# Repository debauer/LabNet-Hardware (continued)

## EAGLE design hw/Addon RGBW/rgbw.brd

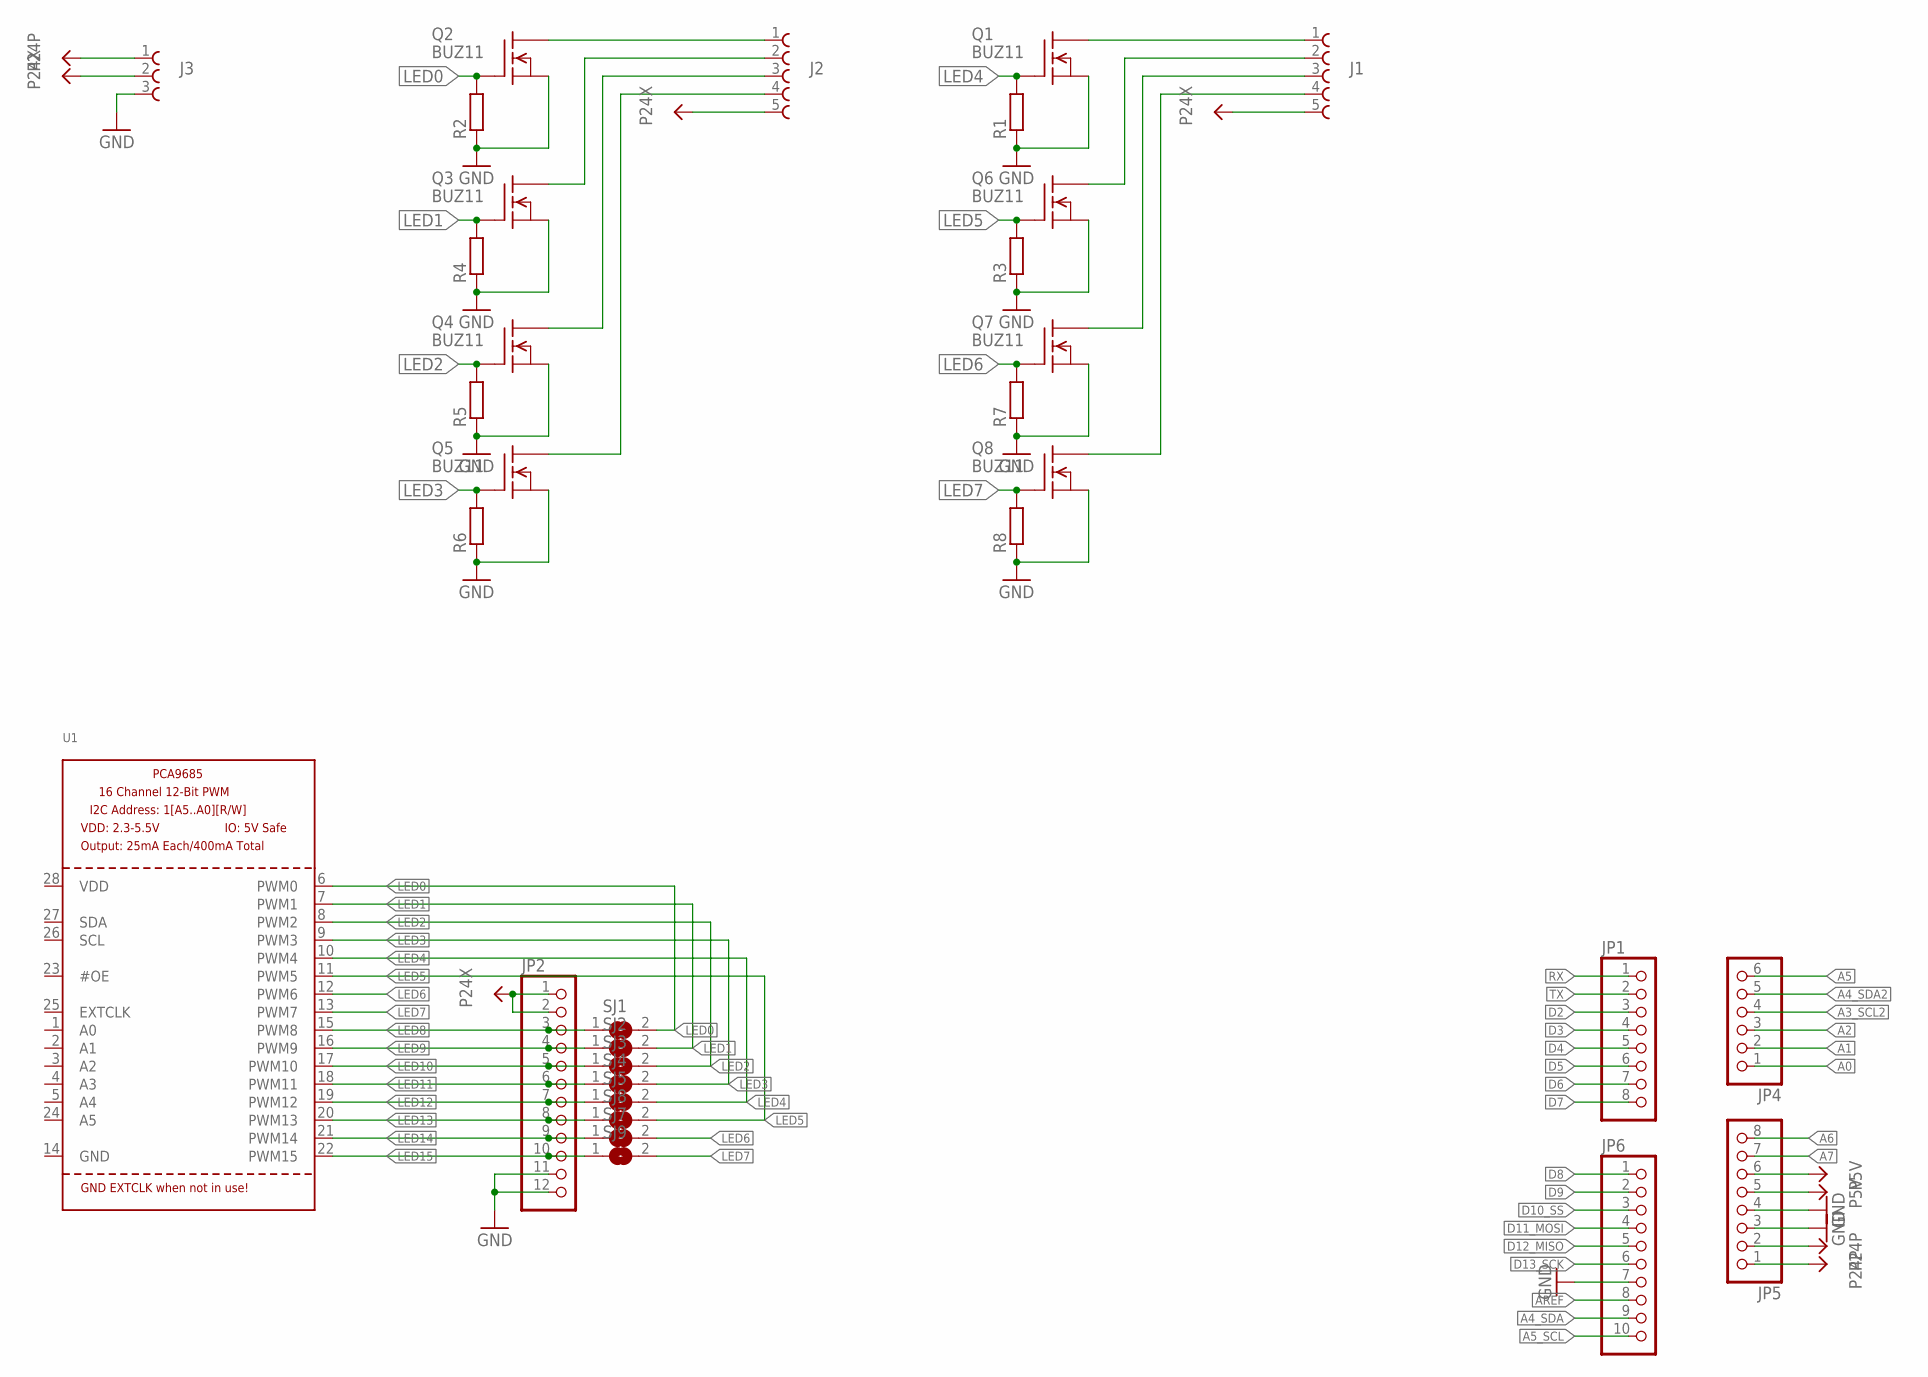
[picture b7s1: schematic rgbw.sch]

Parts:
J1, J2: 691322310005
J3: 691313510003
JP1, JP5: PINHD-1X8; 1X08
JP2: PINHD-1X12; 1X12
JP4: PINHD-1X6; 1X06
JP6: PINHD-1X10; 1X10
Q1, Q2, Q3, Q4, Q5, Q6, Q7, Q8: BUZ11; TO220V
R1, R2, R3, R4, R5, R6, R7, R8: R-EU_R0805; R0805
SJ1, SJ2, SJ3, SJ4, SJ5, SJ7, SJ8, SJ9: SJ
U1: PCA9685; TSSOP28

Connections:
A0: JP4.1
A1: JP4.2
A2: JP4.3
A3_SCL2: JP4.4
A4_SDA: JP6.9
A4_SDA2: JP4.5
A5: JP4.6
A5_SCL: JP6.10
A6: JP5.8
A7: JP5.7
AREF: JP6.8
D2: JP1.3
D3: JP1.4
D4: JP1.5
D5: JP1.6
D6: JP1.7
D7: JP1.8
D8: JP6.1
D9: JP6.2
D10_SS: JP6.3
D11_MOSI: JP6.4
D12_MISO: JP6.5
D13_SCK: JP6.6
GND: J3.3, JP2.11, JP2.12, JP5.3, JP5.4, JP6.7, Q1.3 (S), Q2.3 (S), Q3.3 (S), Q4.3 (S), Q5.3 (S), Q6.3 (S), Q7.3 (S), Q8.3 (S), R1.1, R2.1, R3.1, R4.1, R5.1, R6.1, R7.1, R8.1, U1.14 (GND)
LED0: Q2.1 (G), R2.2, SJ1.2, U1.6 (PWM0)
LED1: Q3.1 (G), R4.2, SJ2.2, U1.7 (PWM1)
LED2: Q4.1 (G), R5.2, SJ3.2, U1.8 (PWM2)
LED3: Q5.1 (G), R6.2, SJ4.2, U1.9 (PWM3)
LED4: Q1.1 (G), R1.2, SJ5.2, U1.10 (PWM4)
LED5: Q6.1 (G), R3.2, SJ8.2, U1.11 (PWM5)
LED6: Q7.1 (G), R7.2, SJ7.2, U1.12 (PWM6)
LED7: Q8.1 (G), R8.2, SJ9.2, U1.13 (PWM7)
LED8: JP2.3, SJ1.1, U1.15 (PWM8)
LED9: JP2.4, SJ2.1, U1.16 (PWM9)
LED10: JP2.5, SJ3.1, U1.17 (PWM10)
LED11: JP2.6, SJ4.1, U1.18 (PWM11)
LED12: JP2.7, SJ5.1, U1.19 (PWM12)
LED13: JP2.8, SJ8.1, U1.20 (PWM13)
LED14: JP2.9, SJ7.1, U1.21 (PWM14)
LED15: JP2.10, SJ9.1, U1.22 (PWM15)
unnamed: J2.1, Q2.2 (D)
unnamed: J2.2, Q3.2 (D)
unnamed: J1.3, Q7.2 (D)
unnamed: J2.3, Q4.2 (D)
unnamed: J2.4, Q5.2 (D)
unnamed: J1.4, Q8.2 (D)
unnamed: J1.1, Q1.2 (D)
unnamed: J1.2, Q6.2 (D)
P5V: JP5.5, JP5.6
P24P: J3.1, JP5.1, JP5.2
P24X: J1.5, J2.5, J3.2, JP2.1, JP2.2
RX: JP1.1
TX: JP1.2
VDD: U1.28 (VDD)

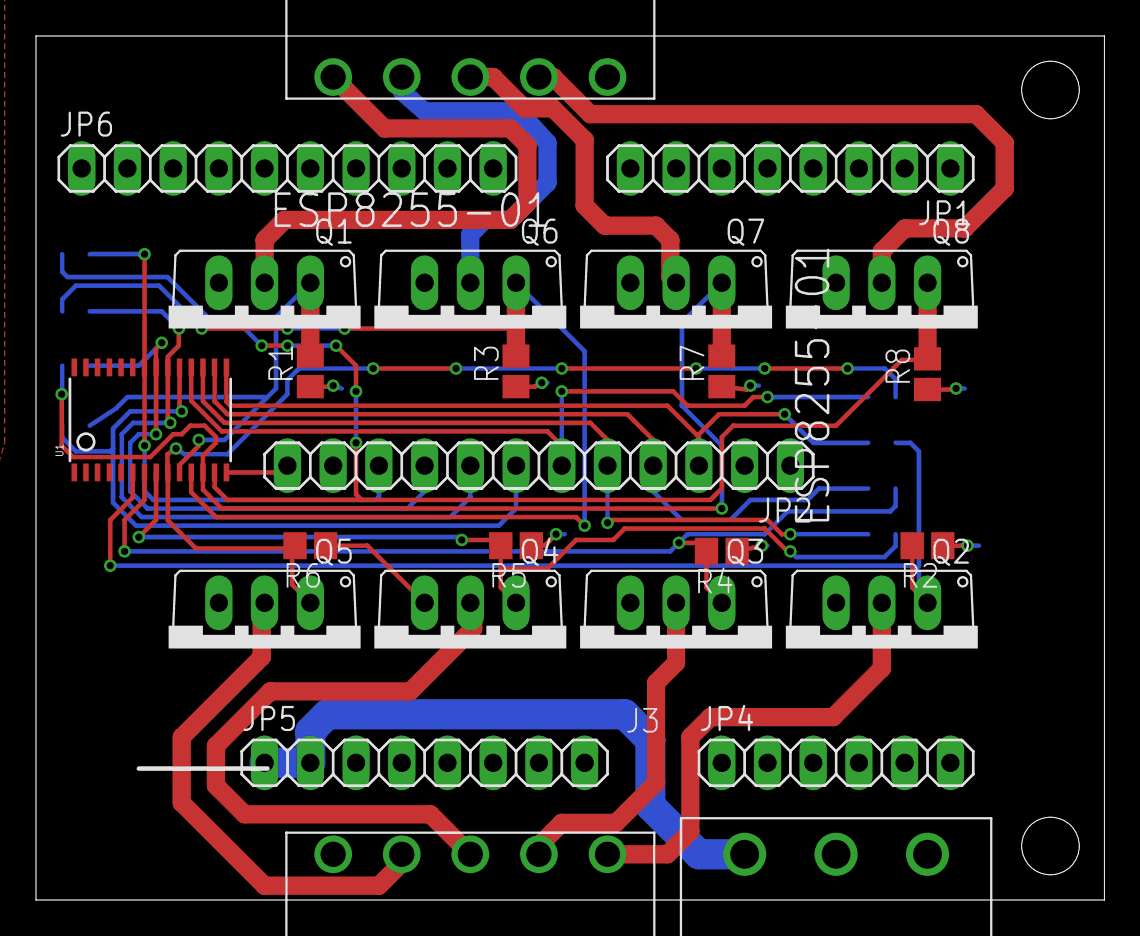
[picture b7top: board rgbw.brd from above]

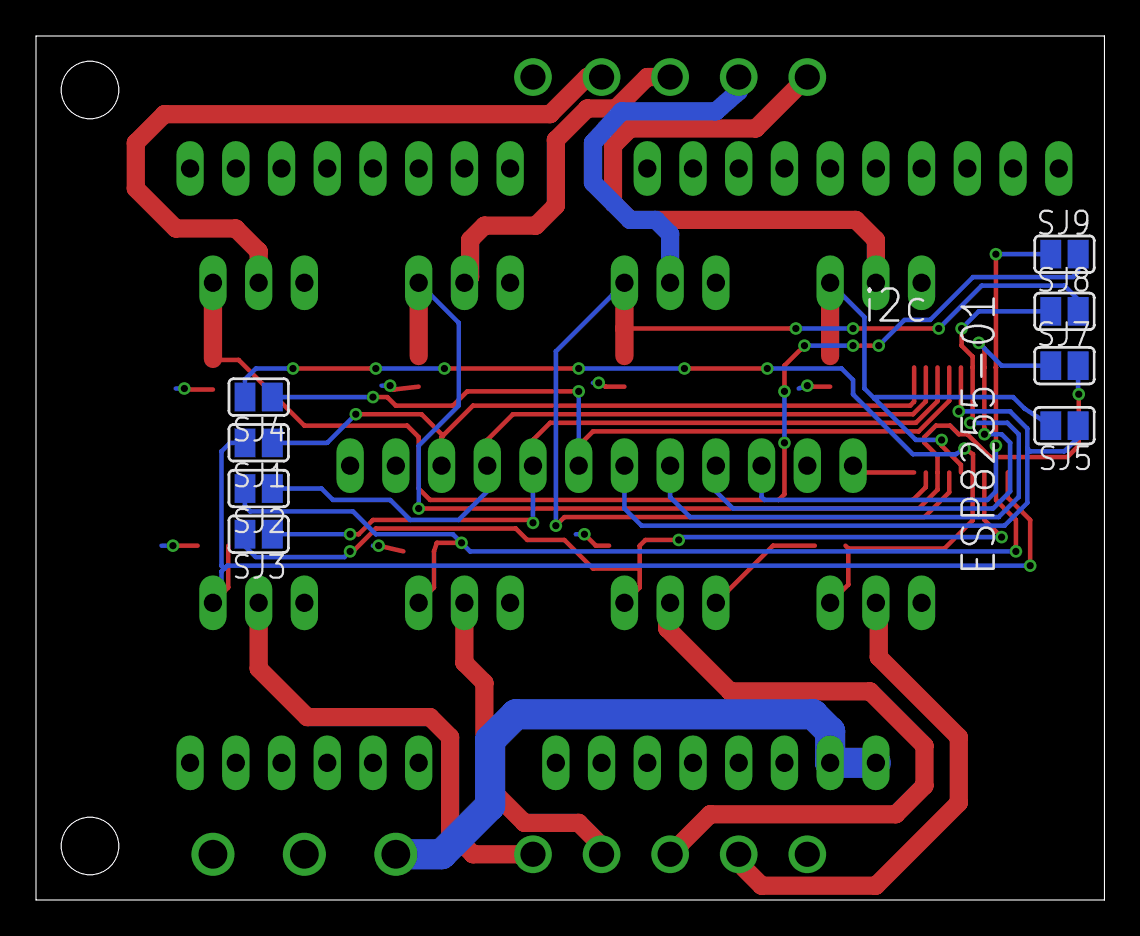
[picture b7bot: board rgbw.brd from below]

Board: 2 copper layers, 59.4 x 48.0 mm, 33 parts (8 on the bottom side), 28 nets.
